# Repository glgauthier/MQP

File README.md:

# FPGA-Based Real-Time SLAM

This repository contains code and miscellaneous content for our [Major Qualifying Project](https://www.wpi.edu/academics/ece/mqp.html). 

This project created a proof of concept SLAM sensor suite capable of remotely observing and mapping areas by combining real-time stereo camera imagery with distance measurements and localization data to generate a 3D depth map and 2D floorplan of its environment. The system used a Xilinx Zynq SoC containing an embedded ARM processor and FPGA fabric, and implemented unique SLAM processing functionality using both embedded software and parallelized custom logic.

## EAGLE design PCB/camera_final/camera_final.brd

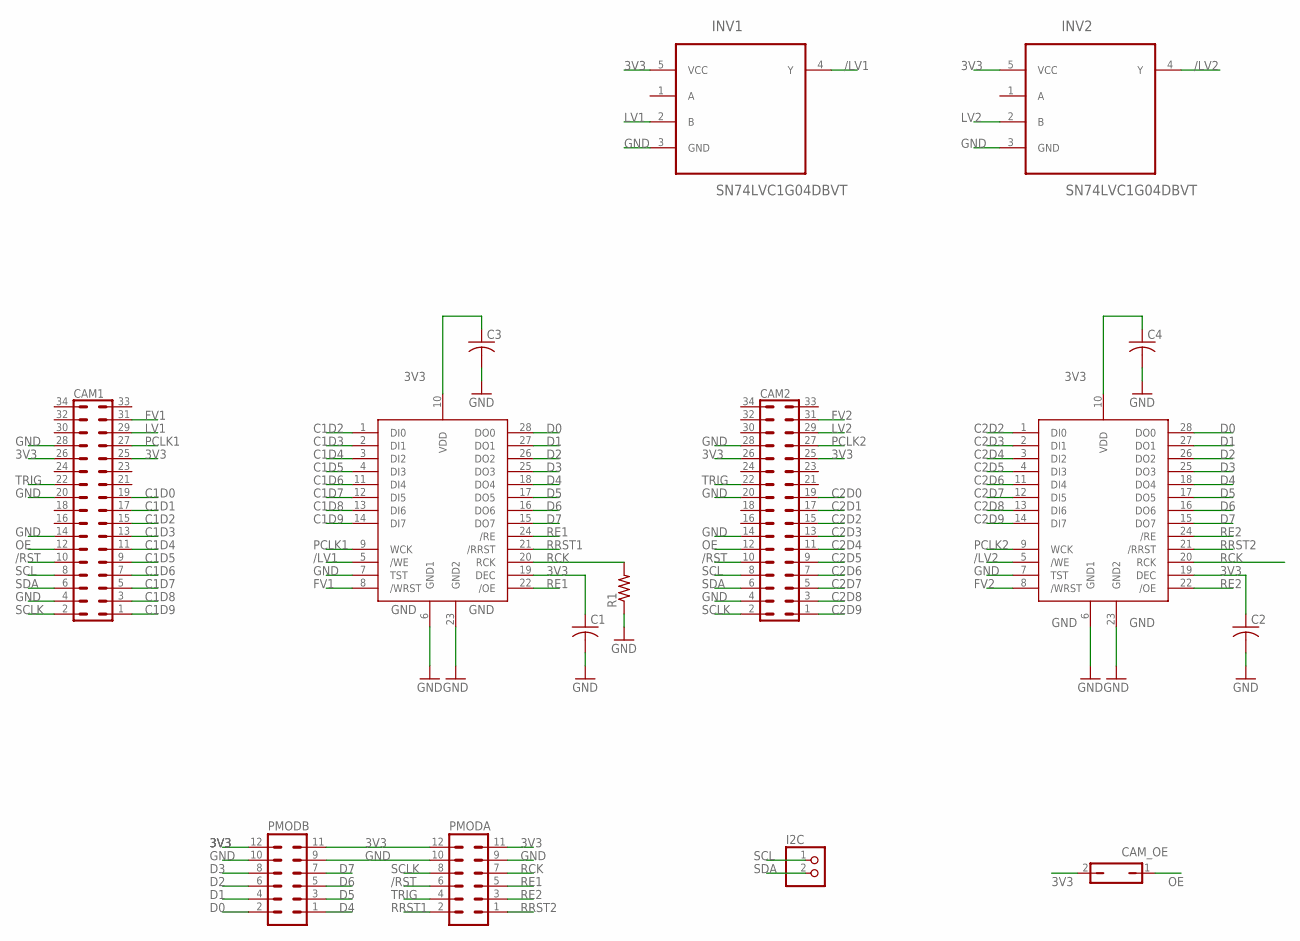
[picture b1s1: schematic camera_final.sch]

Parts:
C1, C2, C3, C4: C-USC0805K; C0805K
CAM1, CAM2: PHB_1MM27_2X17_SNT
CAM_OE: JP1Q; JP1
I2C: PINHD-1X2; 1X02
INV1, INV2: SN74LVC1G04DBVT; SOT95P280X145-5N
PMODA: MA06-2
PMODB: MA06-2
R1: R-US_R0805; R0805
U$1, U$2: AL422B; SOP28

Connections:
3V3: C1.1, C2.1, C3.1, C4.1, CAM1.25, CAM1.26, CAM2.25, CAM2.26, CAM_OE.2, INV1.5 (VCC), INV2.5 (VCC), PMODA.11, PMODA.12, PMODB.11, PMODB.12, U$1.10 (VDD), U$1.19 (DEC), U$2.10 (VDD), U$2.19 (DEC)
/LV1: INV1.4 (Y), U$2.5 (/WE)
/LV2: INV2.4 (Y), U$1.5 (/WE)
/RST: CAM1.10, CAM2.10, PMODA.6
C1D0: CAM1.19
C1D1: CAM1.17
C1D2: CAM1.15, U$2.1 (DI0)
C1D3: CAM1.13, U$2.2 (DI1)
C1D4: CAM1.11, U$2.3 (DI2)
C1D5: CAM1.9, U$2.4 (DI3)
C1D6: CAM1.7, U$2.11 (DI4)
C1D7: CAM1.5, U$2.12 (DI5)
C1D8: CAM1.3, U$2.13 (DI6)
C1D9: CAM1.1, U$2.14 (DI7)
C2D0: CAM2.19
C2D1: CAM2.17
C2D2: CAM2.15, U$1.1 (DI0)
C2D3: CAM2.13, U$1.2 (DI1)
C2D4: CAM2.11, U$1.3 (DI2)
C2D5: CAM2.9, U$1.4 (DI3)
C2D6: CAM2.7, U$1.11 (DI4)
C2D7: CAM2.5, U$1.12 (DI5)
C2D8: CAM2.3, U$1.13 (DI6)
C2D9: CAM2.1, U$1.14 (DI7)
D0: PMODB.2, U$1.28 (DO0), U$2.28 (DO0)
D1: PMODB.4, U$1.27 (DO1), U$2.27 (DO1)
D2: PMODB.6, U$1.26 (DO2), U$2.26 (DO2)
D3: PMODB.8, U$1.25 (DO3), U$2.25 (DO3)
D4: PMODB.1, U$1.18 (DO4), U$2.18 (DO4)
D5: PMODB.3, U$1.17 (DO5), U$2.17 (DO5)
D6: PMODB.5, U$1.16 (DO6), U$2.16 (DO6)
D7: PMODB.7, U$1.15 (DO7), U$2.15 (DO7)
FV1: CAM1.31, U$2.8 (/WRST)
FV2: CAM2.31, U$1.8 (/WRST)
GND: C1.2, C2.2, C3.2, C4.2, CAM1.4, CAM1.14, CAM1.20, CAM1.28, CAM2.4, CAM2.14, CAM2.20, CAM2.28, INV1.3 (GND), INV2.3 (GND), PMODA.9, PMODA.10, PMODB.9, PMODB.10, R1.1, U$1.6 (GND1), U$1.7 (TST), U$1.23 (GND2), U$2.6 (GND1), U$2.7 (TST), U$2.23 (GND2)
LV1: CAM1.29, INV1.2 (B)
LV2: CAM2.29, INV2.2 (B)
OE: CAM1.12, CAM2.12, CAM_OE.1
PCLK1: CAM1.27, U$2.9 (WCK)
PCLK2: CAM2.27, U$1.9 (WCK)
RCK: PMODA.7, R1.2, U$1.20 (RCK), U$2.20 (RCK)
RE1: PMODA.5, U$2.22 (/OE), U$2.24 (/RE)
RE2: PMODA.3, U$1.22 (/OE), U$1.24 (/RE)
RRST1: PMODA.2, U$2.21 (/RRST)
RRST2: PMODA.1, U$1.21 (/RRST)
SCL: CAM1.8, CAM2.8, I2C.1
SCLK: CAM1.2, CAM2.2, PMODA.8
SDA: CAM1.6, CAM2.6, I2C.2
TRIG: CAM1.22, CAM2.22, PMODA.4

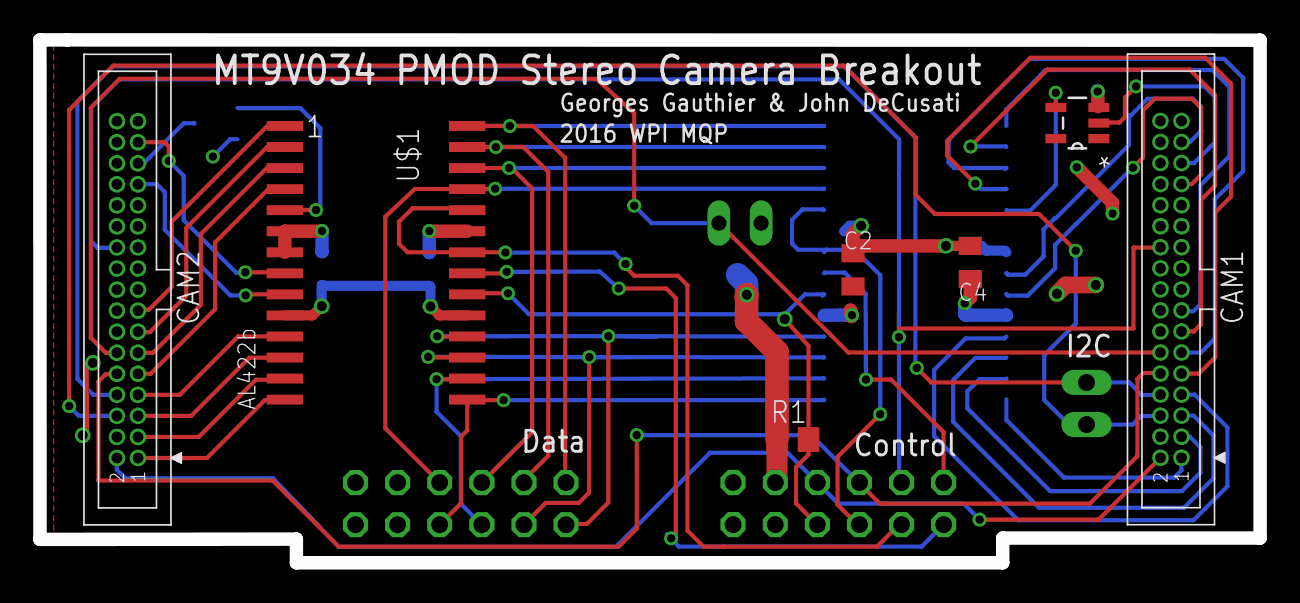
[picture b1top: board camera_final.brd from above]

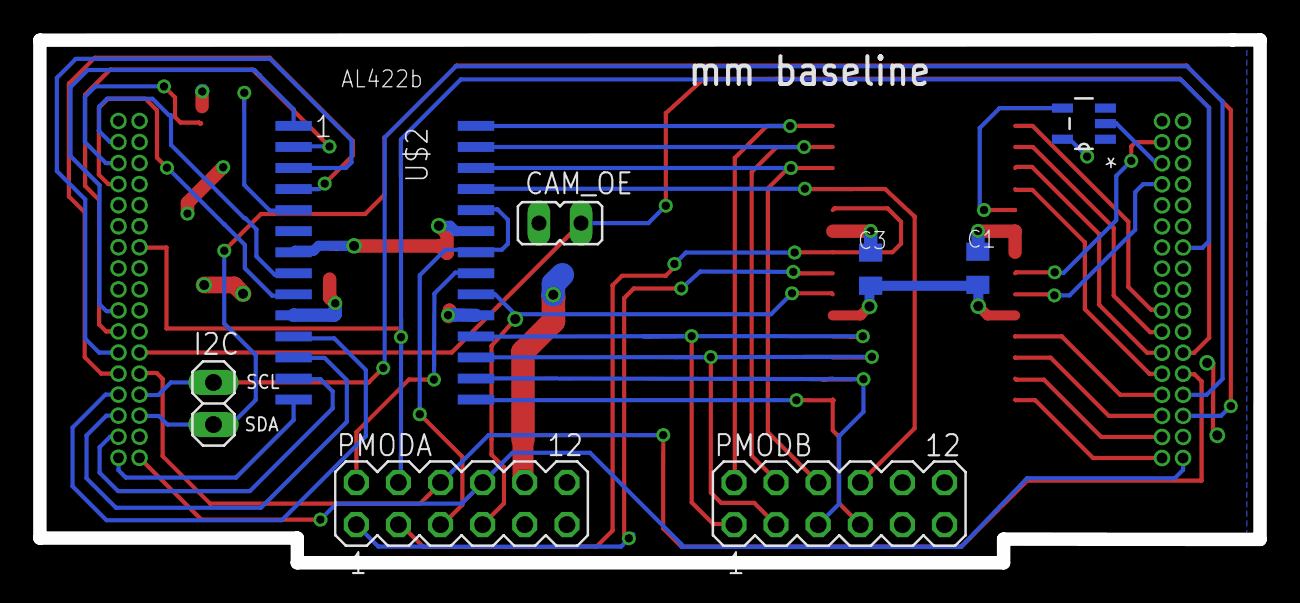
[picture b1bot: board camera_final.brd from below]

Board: 2 copper layers, 73.6 x 31.5 mm, 15 parts (8 on the bottom side), 45 nets.

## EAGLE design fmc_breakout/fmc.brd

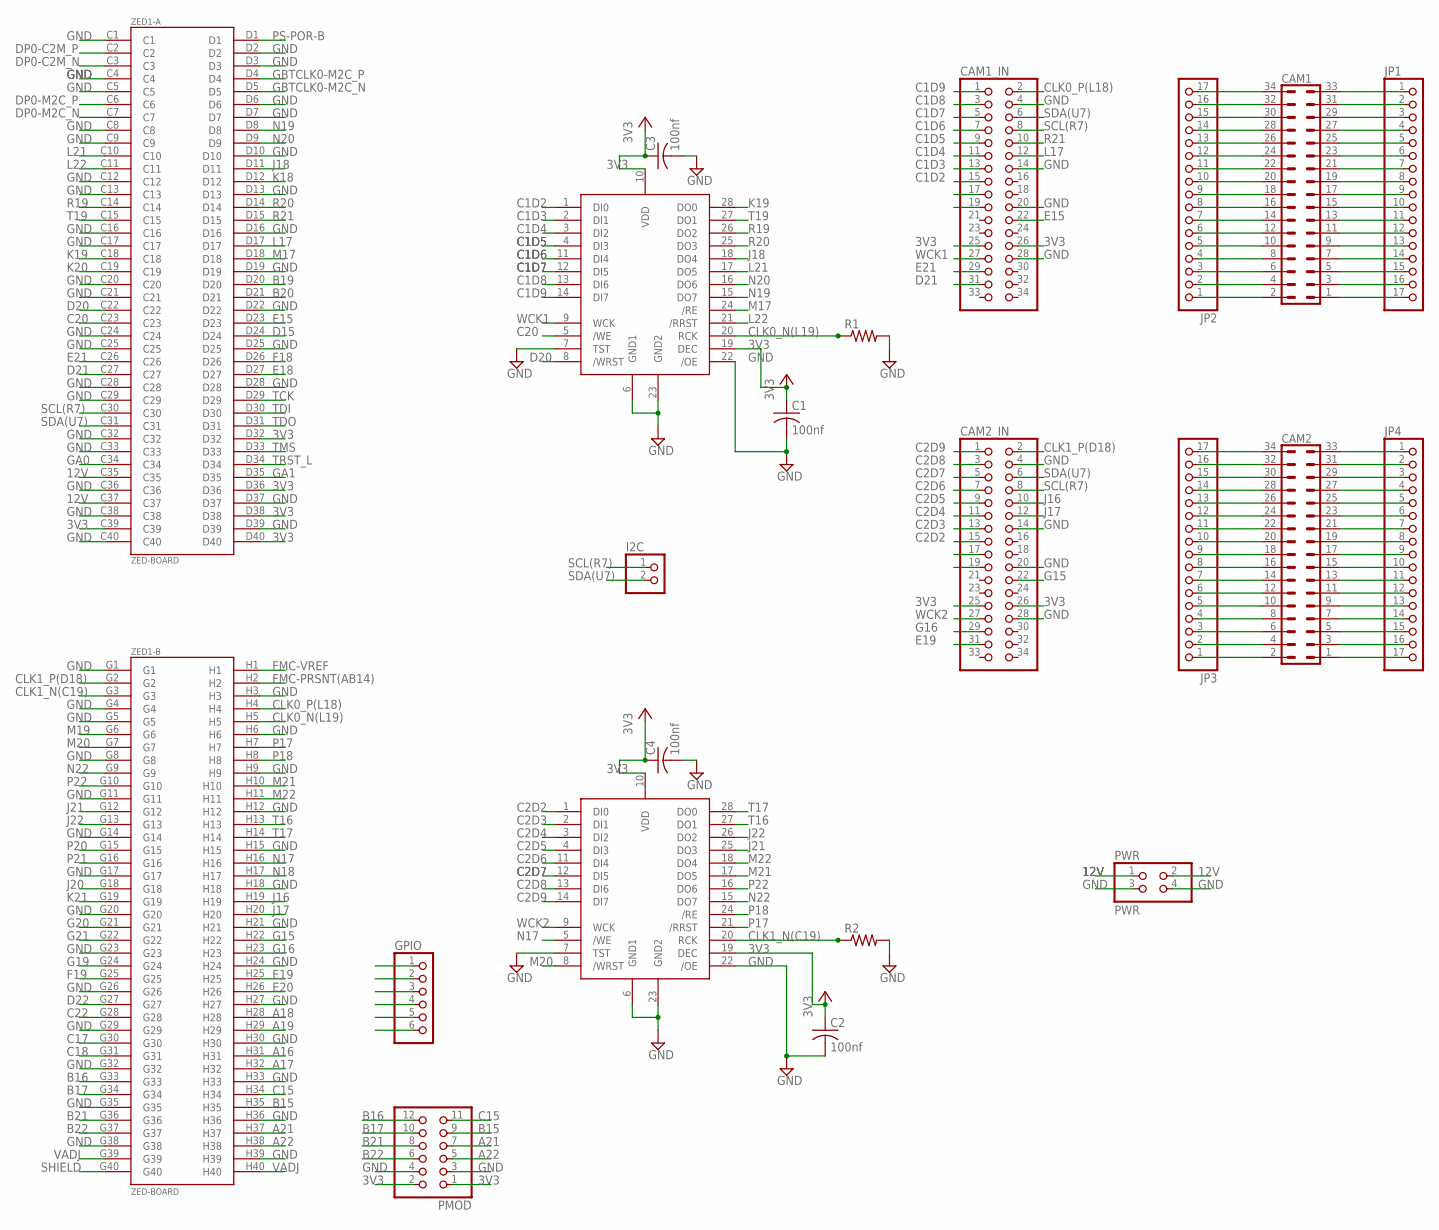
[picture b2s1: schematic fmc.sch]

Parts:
AL422B_2: CAM2_FIFO; SOP28
ALA22B_1: CAM1_FIFO; SOP28
C1, C2, C3, C4: 100nf; C025-024X044
CAM1, CAM2: PHB_1MM27_2X17_SNT
CAM1_IN, CAM2_IN: PINHD-2X17; 2X17
GPIO: PINHD-1X6; 1X06
I2C: PINHD-1X2; 1X02
JP1, JP2, JP3, JP4: PINHD-1X17; 1X17
PMOD: PINHD-2X6; 2X06
PWR: PWR; 2X02
R1, R2: R-US_M0805; M0805
ZED1: ZED-BOARD; ASP-134604-01

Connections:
3V3: AL422B_2.10 (VDD), AL422B_2.19 (DEC), ALA22B_1.10 (VDD), ALA22B_1.19 (DEC), C1.1, C2.1, C3.1, C4.1, CAM1_IN.25, CAM1_IN.26, CAM2_IN.25, CAM2_IN.26, GPIO.6, PMOD.1, PMOD.2, ZED1.C39, ZED1.D32, ZED1.D36, ZED1.D38, ZED1.D40
12V: PWR.1, PWR.2, ZED1.C35, ZED1.C37
A16: GPIO.3, ZED1.H31
A17: GPIO.4, ZED1.H32
A18: GPIO.1, ZED1.H28
A19: GPIO.2, ZED1.H29
A21: PMOD.7, ZED1.H37
A22: PMOD.5, ZED1.H38
B15: PMOD.9, ZED1.H35
B16: PMOD.12, ZED1.G33
B17: PMOD.10, ZED1.G34
B19: ZED1.D20
B20: ZED1.D21
B21: PMOD.8, ZED1.G36
B22: PMOD.6, ZED1.G37
C1D2: ALA22B_1.1 (DI0), CAM1_IN.15
C1D3: ALA22B_1.2 (DI1), CAM1_IN.13
C1D4: ALA22B_1.3 (DI2), CAM1_IN.11
C1D5: ALA22B_1.4 (DI3), CAM1_IN.9
C1D6: ALA22B_1.11 (DI4), CAM1_IN.7
C1D7: ALA22B_1.12 (DI5), CAM1_IN.5
C1D8: ALA22B_1.13 (DI6), CAM1_IN.3
C1D9: ALA22B_1.14 (DI7), CAM1_IN.1
C2D2: AL422B_2.1 (DI0), CAM2_IN.15
C2D3: AL422B_2.2 (DI1), CAM2_IN.13
C2D4: AL422B_2.3 (DI2), CAM2_IN.11
C2D5: AL422B_2.4 (DI3), CAM2_IN.9
C2D6: AL422B_2.11 (DI4), CAM2_IN.7
C2D7: AL422B_2.12 (DI5), CAM2_IN.5
C2D8: AL422B_2.13 (DI6), CAM2_IN.3
C2D9: AL422B_2.14 (DI7), CAM2_IN.1
C15: PMOD.11, ZED1.H34
C17: ZED1.G30
C18: ZED1.G31
C20: ALA22B_1.5 (/WE), ZED1.C23
C22: ZED1.G28
CLK0_N(L19): ALA22B_1.20 (RCK), R1.1, ZED1.H5
CLK0_P(L18): CAM1_IN.2, ZED1.H4
CLK1_N(C19): AL422B_2.20 (RCK), R2.1, ZED1.G3
CLK1_P(D18): CAM2_IN.2, ZED1.G2
D15: ZED1.D24
D20: ALA22B_1.8 (/WRST), ZED1.C22
D21: CAM1_IN.31, ZED1.C27
D22: ZED1.G27
DP0-C2M_N: ZED1.C3
DP0-C2M_P: ZED1.C2
DP0-M2C_N: ZED1.C7
DP0-M2C_P: ZED1.C6
E15: CAM1_IN.22, ZED1.D23
E18: ZED1.D27
E19: CAM2_IN.31, ZED1.H25
E20: ZED1.H26
E21: CAM1_IN.29, ZED1.C26
F18: ZED1.D26
F19: ZED1.G25
FMC-PRSNT(AB14): ZED1.H2
FMC-VREF: ZED1.H1
G15: CAM2_IN.22, ZED1.H22
G16: CAM2_IN.29, ZED1.H23
G19: ZED1.G24
G20: ZED1.G21
G21: ZED1.G22
GA0: ZED1.C34
GA1: ZED1.D35
GBTCLK0-M2C_N: ZED1.D5
GBTCLK0-M2C_P: ZED1.D4
GND: AL422B_2.6 (GND1), AL422B_2.7 (TST), AL422B_2.22 (/OE), AL422B_2.23 (GND2), ALA22B_1.6 (GND1), ALA22B_1.7 (TST), ALA22B_1.22 (/OE), ALA22B_1.23 (GND2), C1.2, C2.2, C3.2, C4.2, CAM1_IN.4, CAM1_IN.14, CAM1_IN.20, CAM1_IN.28, CAM2_IN.4, CAM2_IN.14, CAM2_IN.20, CAM2_IN.28, GPIO.5, PMOD.3, PMOD.4, PWR.3, PWR.4, R1.2, R2.2, ZED1.C1, ZED1.C4, ZED1.C5, ZED1.C8, ZED1.C9, ZED1.C12, ZED1.C13, ZED1.C16, ZED1.C17, ZED1.C20, ZED1.C21, ZED1.C24, ZED1.C25, ZED1.C28, ZED1.C29, ZED1.C32, ZED1.C33, ZED1.C36, ZED1.C38, ZED1.C40, ZED1.D2, ZED1.D3, ZED1.D6, ZED1.D7, ZED1.D10, ZED1.D13, ZED1.D16, ZED1.D19, ZED1.D22, ZED1.D25, ZED1.D28, ZED1.D37, ZED1.D39, ZED1.G1, ZED1.G4, ZED1.G5, ZED1.G8, ZED1.G11, ZED1.G14, ZED1.G17, ZED1.G20, ZED1.G23, ZED1.G26, ZED1.G29, ZED1.G32, ZED1.G35, ZED1.G38, ZED1.H3, ZED1.H6, ZED1.H9, ZED1.H12, ZED1.H15, ZED1.H18, ZED1.H21, ZED1.H24, ZED1.H27, ZED1.H30, ZED1.H33, ZED1.H36, ZED1.H39
J16: CAM2_IN.10, ZED1.H19
J17: CAM2_IN.12, ZED1.H20
J18: ALA22B_1.18 (DO4), ZED1.D11
J20: ZED1.G18
J21: AL422B_2.25 (DO3), ZED1.G12
J22: AL422B_2.26 (DO2), ZED1.G13
K18: ZED1.D12
K19: ALA22B_1.28 (DO0), ZED1.C18
K20: ZED1.C19
K21: ZED1.G19
L17: CAM1_IN.12, ZED1.D17
L21: ALA22B_1.17 (DO5), ZED1.C10
L22: ALA22B_1.21 (/RRST), ZED1.C11
M17: ALA22B_1.24 (/RE), ZED1.D18
M19: ZED1.G6
M20: AL422B_2.8 (/WRST), ZED1.G7
M21: AL422B_2.17 (DO5), ZED1.H10
M22: AL422B_2.18 (DO4), ZED1.H11
N17: AL422B_2.5 (/WE), ZED1.H16
N18: ZED1.H17
N19: ALA22B_1.15 (DO7), ZED1.D8
N20: ALA22B_1.16 (DO6), ZED1.D9
N22: AL422B_2.15 (DO7), ZED1.G9
unnamed: CAM1.34, JP2.17
unnamed: CAM1.32, JP2.16
unnamed: CAM1.30, JP2.15
unnamed: CAM1.28, JP2.14
unnamed: CAM1.26, JP2.13
unnamed: CAM1.24, JP2.12
unnamed: CAM1.22, JP2.11
unnamed: CAM1.20, JP2.10
unnamed: CAM1.18, JP2.9
unnamed: CAM1.16, JP2.8
unnamed: CAM1.14, JP2.7
unnamed: CAM1.12, JP2.6
unnamed: CAM1.10, JP2.5
unnamed: CAM1.8, JP2.4
unnamed: CAM1.6, JP2.3
unnamed: CAM1.4, JP2.2
unnamed: CAM1.2, JP2.1
unnamed: CAM1.33, JP1.1
unnamed: CAM1.31, JP1.2
unnamed: CAM1.29, JP1.3
unnamed: CAM1.27, JP1.4
unnamed: CAM1.25, JP1.5
unnamed: CAM1.23, JP1.6
unnamed: CAM1.21, JP1.7
unnamed: CAM1.19, JP1.8
unnamed: CAM1.17, JP1.9
unnamed: CAM1.15, JP1.10
unnamed: CAM1.13, JP1.11
unnamed: CAM1.11, JP1.12
unnamed: CAM1.9, JP1.13
unnamed: CAM1.7, JP1.14
unnamed: CAM1.5, JP1.15
unnamed: CAM1.3, JP1.16
unnamed: CAM1.1, JP1.17
unnamed: CAM2.33, JP4.1
unnamed: CAM2.31, JP4.2
unnamed: CAM2.29, JP4.3
unnamed: CAM2.27, JP4.4
unnamed: CAM2.25, JP4.5
unnamed: CAM2.23, JP4.6
unnamed: CAM2.21, JP4.7
unnamed: CAM2.19, JP4.8
unnamed: CAM2.17, JP4.9
unnamed: CAM2.15, JP4.10
unnamed: CAM2.13, JP4.11
unnamed: CAM2.11, JP4.12
unnamed: CAM2.9, JP4.13
unnamed: CAM2.7, JP4.14
unnamed: CAM2.5, JP4.15
unnamed: CAM2.3, JP4.16
unnamed: CAM2.1, JP4.17
unnamed: CAM2.34, JP3.17
unnamed: CAM2.32, JP3.16
unnamed: CAM2.30, JP3.15
unnamed: CAM2.28, JP3.14
unnamed: CAM2.26, JP3.13
unnamed: CAM2.24, JP3.12
unnamed: CAM2.22, JP3.11
unnamed: CAM2.20, JP3.10
unnamed: CAM2.18, JP3.9
unnamed: CAM2.16, JP3.8
unnamed: CAM2.14, JP3.7
unnamed: CAM2.12, JP3.6
unnamed: CAM2.10, JP3.5
unnamed: CAM2.8, JP3.4
unnamed: CAM2.6, JP3.3
unnamed: CAM2.4, JP3.2
unnamed: CAM2.2, JP3.1
P17: AL422B_2.21 (/RRST), ZED1.H7
P18: AL422B_2.24 (/RE), ZED1.H8
P20: ZED1.G15
P21: ZED1.G16
P22: AL422B_2.16 (DO6), ZED1.G10
PS-POR-B: ZED1.D1
R19: ALA22B_1.26 (DO2), ZED1.C14
R20: ALA22B_1.25 (DO3), ZED1.D14
R21: CAM1_IN.10, ZED1.D15
SCL(R7): CAM1_IN.8, CAM2_IN.8, I2C.1, ZED1.C30
SDA(U7): CAM1_IN.6, CAM2_IN.6, I2C.2, ZED1.C31
SHIELD: ZED1.G40
T16: AL422B_2.27 (DO1), ZED1.H13
T17: AL422B_2.28 (DO0), ZED1.H14
T19: ALA22B_1.27 (DO1), ZED1.C15
TCK: ZED1.D29
TDI: ZED1.D30
TDO: ZED1.D31
TMS: ZED1.D33
TRST_L: ZED1.D34
VADJ: ZED1.G39, ZED1.H40
WCK1: ALA22B_1.9 (WCK), CAM1_IN.27
WCK2: AL422B_2.9 (WCK), CAM2_IN.27

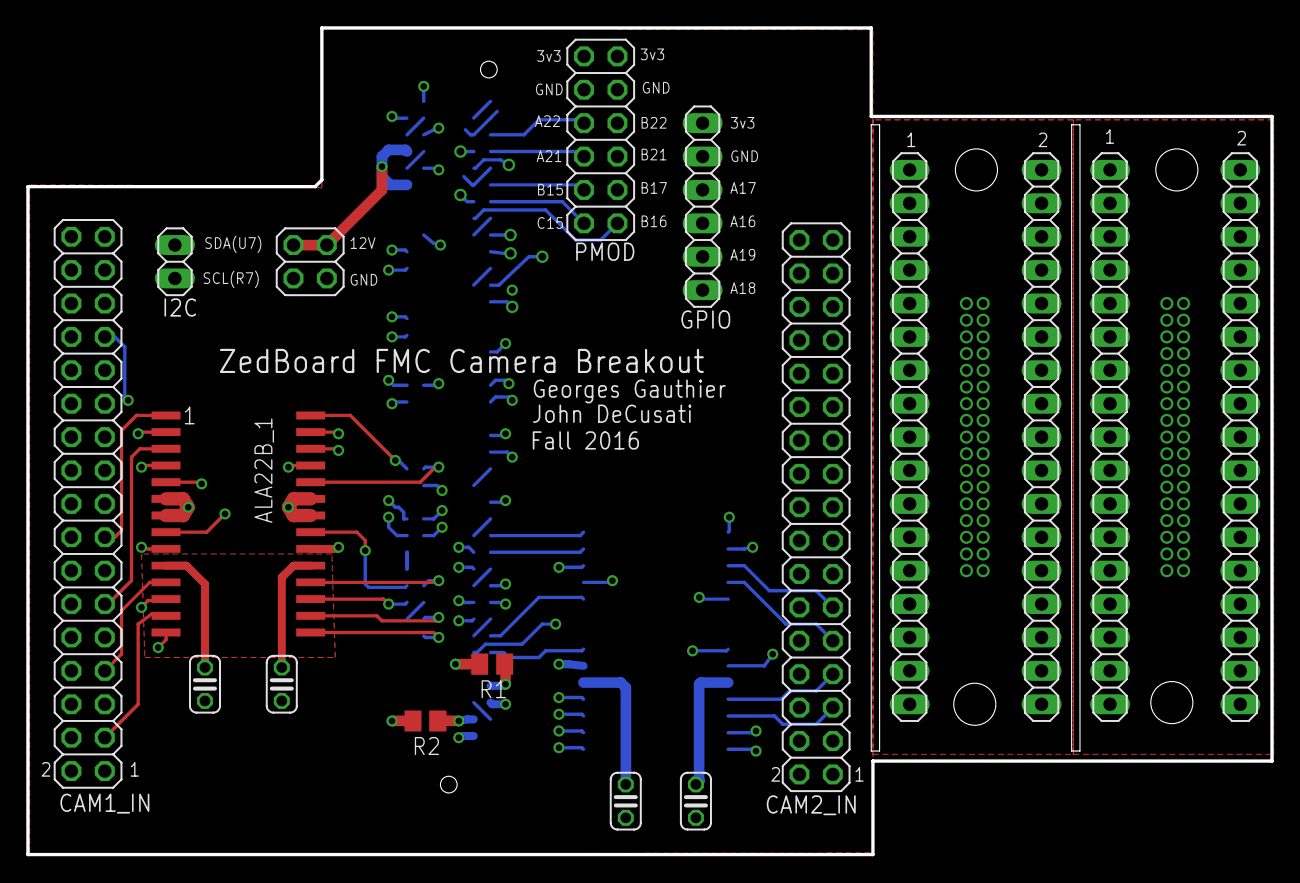
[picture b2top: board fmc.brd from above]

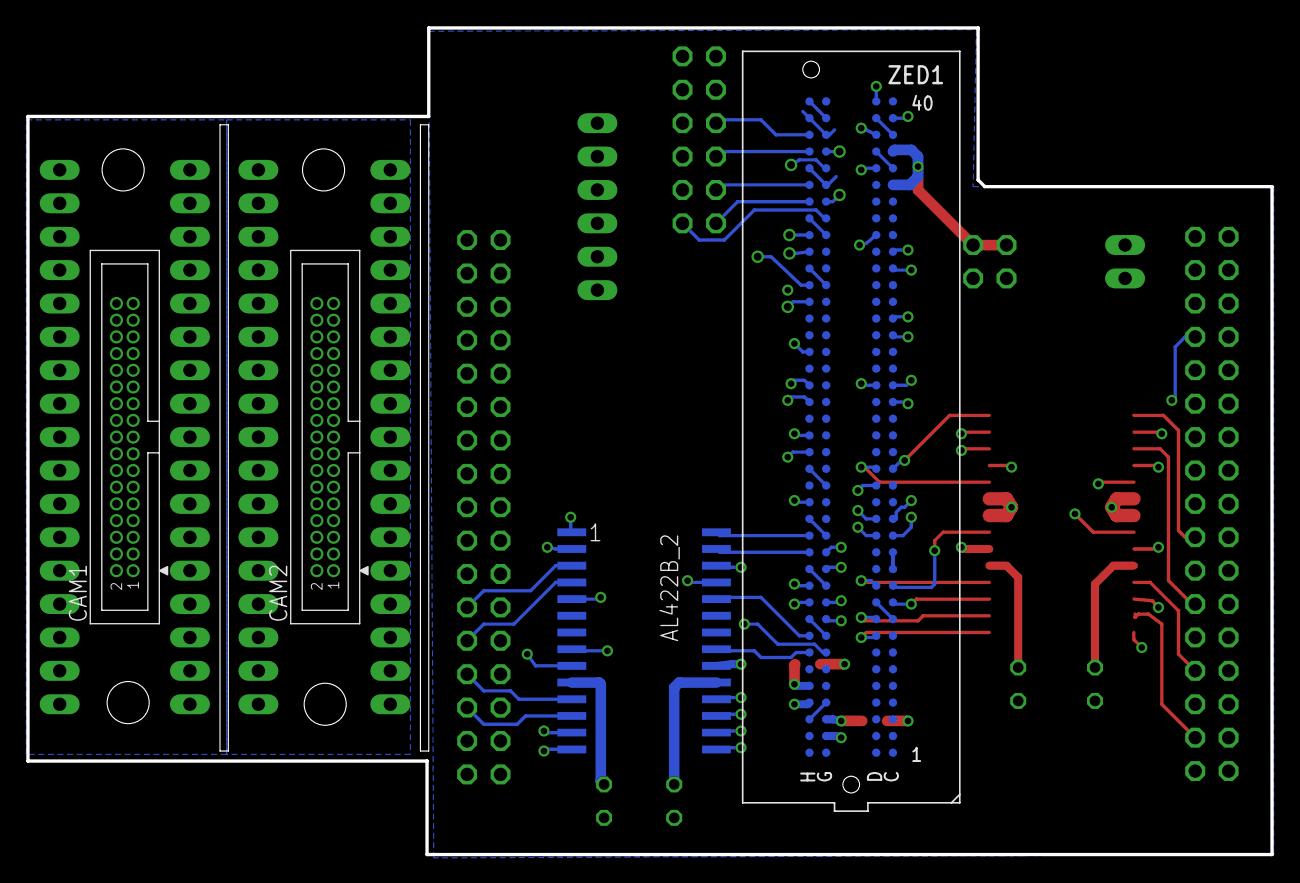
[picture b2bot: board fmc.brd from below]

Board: 4 copper layers, 94.6 x 62.9 mm, 21 parts (4 on the bottom side), 142 nets.

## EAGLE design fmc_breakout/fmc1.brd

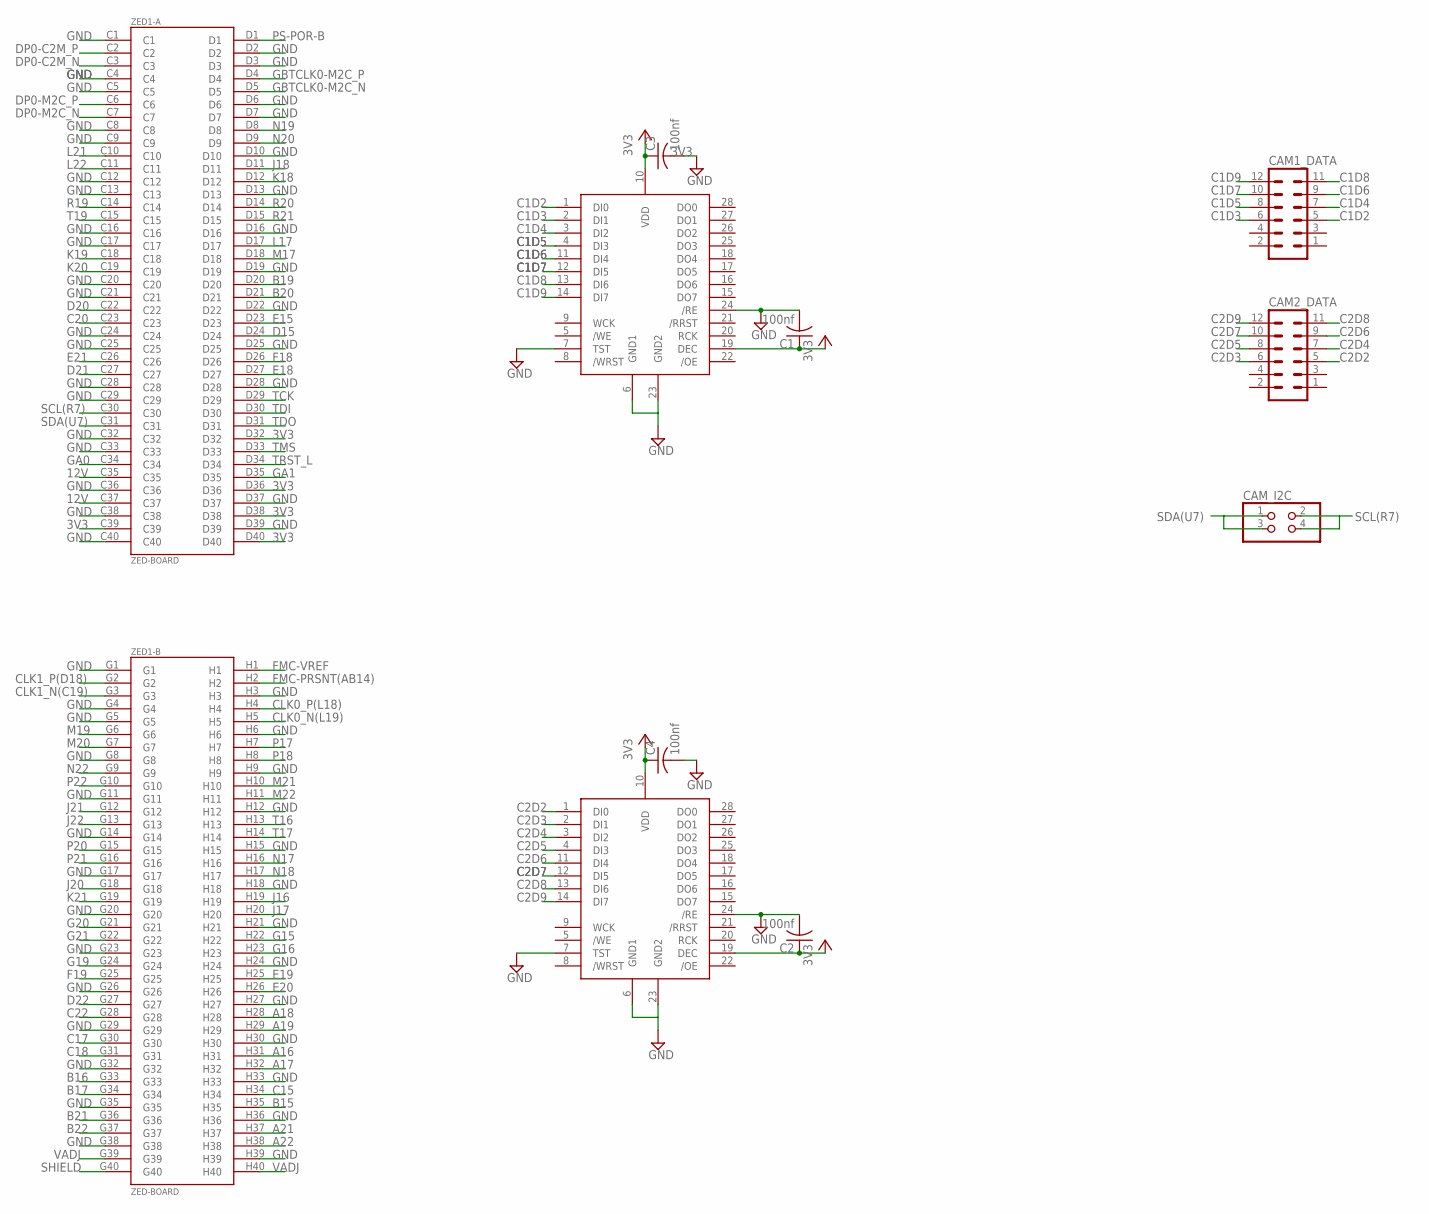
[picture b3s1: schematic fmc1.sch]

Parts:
AL422B: AL422B; SOP28
C1, C2, C3, C4: 100nf; C025-024X044
CAM1_DATA, CAM2_DATA: MA06-2
CAM_I2C: PINHD-2X2; 2X02
U$2: AL422B; SOP28
ZED1: ZED-BOARD; ASP-134604-01

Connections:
3V3: AL422B.10 (VDD), C3.1, C4.1, U$2.10 (VDD), ZED1.C39, ZED1.D32, ZED1.D36, ZED1.D38, ZED1.D40
12V: ZED1.C35, ZED1.C37
+3V3: AL422B.19 (DEC), C1.1, C2.1, U$2.19 (DEC)
A16: ZED1.H31
A17: ZED1.H32
A18: ZED1.H28
A19: ZED1.H29
A21: ZED1.H37
A22: ZED1.H38
B15: ZED1.H35
B16: ZED1.G33
B17: ZED1.G34
B19: ZED1.D20
B20: ZED1.D21
B21: ZED1.G36
B22: ZED1.G37
C1D2: AL422B.1 (DI0), CAM1_DATA.5
C1D3: AL422B.2 (DI1), CAM1_DATA.6
C1D4: AL422B.3 (DI2), CAM1_DATA.7
C1D5: AL422B.4 (DI3), CAM1_DATA.8
C1D6: AL422B.11 (DI4), CAM1_DATA.9
C1D7: AL422B.12 (DI5), CAM1_DATA.10
C1D8: AL422B.13 (DI6), CAM1_DATA.11
C1D9: AL422B.14 (DI7), CAM1_DATA.12
C2D2: CAM2_DATA.5, U$2.1 (DI0)
C2D3: CAM2_DATA.6, U$2.2 (DI1)
C2D4: CAM2_DATA.7, U$2.3 (DI2)
C2D5: CAM2_DATA.8, U$2.4 (DI3)
C2D6: CAM2_DATA.9, U$2.11 (DI4)
C2D7: CAM2_DATA.10, U$2.12 (DI5)
C2D8: CAM2_DATA.11, U$2.13 (DI6)
C2D9: CAM2_DATA.12, U$2.14 (DI7)
C15: ZED1.H34
C17: ZED1.G30
C18: ZED1.G31
C20: ZED1.C23
C22: ZED1.G28
CLK0_N(L19): ZED1.H5
CLK0_P(L18): ZED1.H4
CLK1_N(C19): ZED1.G3
CLK1_P(D18): ZED1.G2
D15: ZED1.D24
D20: ZED1.C22
D21: ZED1.C27
D22: ZED1.G27
DP0-C2M_N: ZED1.C3
DP0-C2M_P: ZED1.C2
DP0-M2C_N: ZED1.C7
DP0-M2C_P: ZED1.C6
E15: ZED1.D23
E18: ZED1.D27
E19: ZED1.H25
E20: ZED1.H26
E21: ZED1.C26
F18: ZED1.D26
F19: ZED1.G25
FMC-PRSNT(AB14): ZED1.H2
FMC-VREF: ZED1.H1
G15: ZED1.H22
G16: ZED1.H23
G19: ZED1.G24
G20: ZED1.G21
G21: ZED1.G22
GA0: ZED1.C34
GA1: ZED1.D35
GBTCLK0-M2C_N: ZED1.D5
GBTCLK0-M2C_P: ZED1.D4
GND: AL422B.6 (GND1), AL422B.7 (TST), AL422B.23 (GND2), AL422B.24 (/RE), C1.2, C2.2, C3.2, C4.2, U$2.6 (GND1), U$2.7 (TST), U$2.23 (GND2), U$2.24 (/RE), ZED1.C1, ZED1.C4, ZED1.C5, ZED1.C8, ZED1.C9, ZED1.C12, ZED1.C13, ZED1.C16, ZED1.C17, ZED1.C20, ZED1.C21, ZED1.C24, ZED1.C25, ZED1.C28, ZED1.C29, ZED1.C32, ZED1.C33, ZED1.C36, ZED1.C38, ZED1.C40, ZED1.D2, ZED1.D3, ZED1.D6, ZED1.D7, ZED1.D10, ZED1.D13, ZED1.D16, ZED1.D19, ZED1.D22, ZED1.D25, ZED1.D28, ZED1.D37, ZED1.D39, ZED1.G1, ZED1.G4, ZED1.G5, ZED1.G8, ZED1.G11, ZED1.G14, ZED1.G17, ZED1.G20, ZED1.G23, ZED1.G26, ZED1.G29, ZED1.G32, ZED1.G35, ZED1.G38, ZED1.H3, ZED1.H6, ZED1.H9, ZED1.H12, ZED1.H15, ZED1.H18, ZED1.H21, ZED1.H24, ZED1.H27, ZED1.H30, ZED1.H33, ZED1.H36, ZED1.H39
J16: ZED1.H19
J17: ZED1.H20
J18: ZED1.D11
J20: ZED1.G18
J21: ZED1.G12
J22: ZED1.G13
K18: ZED1.D12
K19: ZED1.C18
K20: ZED1.C19
K21: ZED1.G19
L17: ZED1.D17
L21: ZED1.C10
L22: ZED1.C11
M17: ZED1.D18
M19: ZED1.G6
M20: ZED1.G7
M21: ZED1.H10
M22: ZED1.H11
N17: ZED1.H16
N18: ZED1.H17
N19: ZED1.D8
N20: ZED1.D9
N22: ZED1.G9
P17: ZED1.H7
P18: ZED1.H8
P20: ZED1.G15
P21: ZED1.G16
P22: ZED1.G10
PS-POR-B: ZED1.D1
R19: ZED1.C14
R20: ZED1.D14
R21: ZED1.D15
SCL(R7): CAM_I2C.2, CAM_I2C.4, ZED1.C30
SDA(U7): CAM_I2C.1, CAM_I2C.3, ZED1.C31
SHIELD: ZED1.G40
T16: ZED1.H13
T17: ZED1.H14
T19: ZED1.C15
TCK: ZED1.D29
TDI: ZED1.D30
TDO: ZED1.D31
TMS: ZED1.D33
TRST_L: ZED1.D34
VADJ: ZED1.G39, ZED1.H40

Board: 2 copper layers, 10 parts (0 on the bottom side), 23 nets, no tracks yet.

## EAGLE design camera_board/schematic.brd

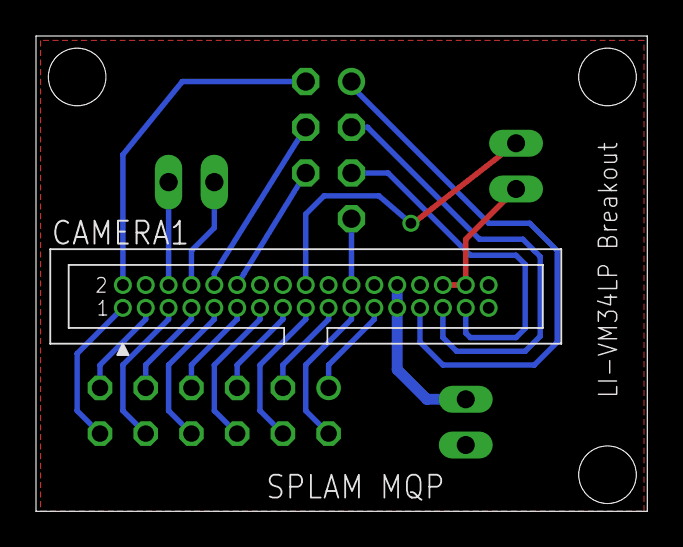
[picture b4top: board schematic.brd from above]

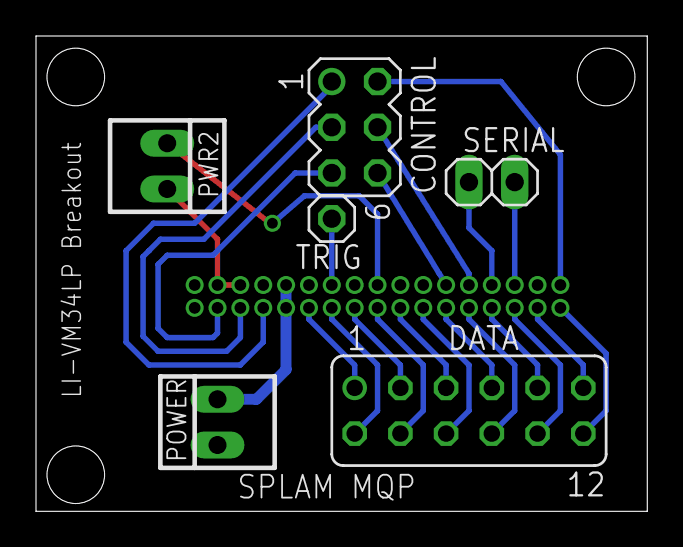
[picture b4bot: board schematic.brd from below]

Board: 2 copper layers, 34.0 x 26.4 mm, 7 parts (6 on the bottom side), 25 nets.

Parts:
CAMERA1: MT9V034; PHB_1MM27_2X17_SNT
CONTROL: MA03-2
DATA: FE06-2
POWER: MAIN; 22-23-2021
PWR2: NC; 22-23-2021
SERIAL: 1X02
TRIG: 1X01

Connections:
1.8V: CAMERA1.30, CAMERA1.32, PWR2.2
2.8V: CAMERA1.18, PWR2.1
GND: CAMERA1.4, CAMERA1.14, CAMERA1.20, CAMERA1.28, POWER.1
unnamed: CAMERA1.23, DATA.1
unnamed: CAMERA1.21, DATA.2
unnamed: CAMERA1.19, DATA.3
unnamed: CAMERA1.17, DATA.4
unnamed: CAMERA1.15, DATA.5
unnamed: CAMERA1.13, DATA.6
unnamed: CAMERA1.11, DATA.7
unnamed: CAMERA1.9, DATA.8
unnamed: CAMERA1.7, DATA.9
unnamed: CAMERA1.5, DATA.10
unnamed: CAMERA1.3, DATA.11
unnamed: CAMERA1.1, DATA.12
unnamed: CAMERA1.12, CONTROL.6
unnamed: CAMERA1.10, CONTROL.4
unnamed: CAMERA1.2, CONTROL.2
unnamed: CAMERA1.31, CONTROL.5
unnamed: CAMERA1.29, CONTROL.3
unnamed: CAMERA1.27, CONTROL.1
unnamed: CAMERA1.8, SERIAL.2
unnamed: CAMERA1.6, SERIAL.1
TRIGGER: CAMERA1.22, TRIG.1
VCC: CAMERA1.25, CAMERA1.26, POWER.2

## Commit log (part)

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2016-05-05 basic web page
    added support for a landing page, about page, and timeline
2016-05-05 updated gh-pages readme.md
2016-05-05 LaTeX report
    Started working on our report in LaTeX. So far I’ve set the following
    up:
    - Formatted title page
    - Support for a Table of Contents w/ clickable links to each section
    - Acknowledgements, Abstract, and Introduction.
    Things I still need to add
2016-05-06 Background, Appendix, Minor Changes
2016-05-26 Started Camera Adapter Schematic
    - Starting with a single camera module for now, then I'll rinse and
    repeat.
    Currently done with PWR/GND and camera shutter trigger. Mapping to the
    PMOD connectors will get interesting...
2016-05-26 Completed Schematic, Started Board
2016-05-27 Updated Schematic and Board
    I'm debating on removing the ccd_data pin breakout all together - more
    to come on this
2016-05-31 removed local schematic location
2016-05-31 Deleted schematic local location
2016-05-31 Final Schematic Part II
    Need to double check and then I'll order boards
2016-05-31 FMC-LPC connector added for future breakout board project
2016-05-31 Added missing pin, finalized(?) board design
    - Missed the trigger pin, that could have been bad!
    - Double checked the layout and it looks correct
    - Passed OSHpark DRC, ERC
2016-07-10 camera reset, eagle cleanup
2016-07-10 rangefinder data
2016-07-11 UART test
    not working
2016-07-13 added BUFG for debounce CLK
    no more warnings!
2016-07-13 writing correct val; ready for tri-state & SM
2016-07-14 camera data
2016-07-15 removed "i2c" code
    not worth the time, found another route. Next up is proper power up
    sequence
2016-07-15 proper initialization sequence, scope data
    it works!
    - full i2c control from 3.3v external micro
    - able to configure control register for external trigger mode
    -> control register isn't saved between OE_N state change, so set OE_N
    high before changing camera control to trigger mode
2016-07-15 started FMC breakout
2016-07-15 FMC bus map
2016-07-15 FMC bus pins mapped to FPGA bank locations
2016-07-16 added camera data headers
2016-07-18 microblaze for camera data over UART
2016-07-19 updated fifo code, screenshots, matlab code
    - Camera -> AL422B FIFO -> Line buffer on FPGA -> Microblaze -> UART. it
    almost works!
2016-07-20 updated matlab script for showing images, cleaned up stuff
2016-07-20 added camera section to methodology
2016-07-21 100% working images
    finally!
    I was leaving FIFO_RDEN on for an extra 2 clock cycles, so my read
    pointer was 2 pixels further ahead of where it should have been for
    every read by the FPGA
2016-07-21 more bug fixes
2016-07-22 updating report
2016-07-22 camera operation
2016-07-22 listings line wrap
2016-07-25 semi-finished documentation of current progress
2016-07-25 proofreading
2016-07-27 Finished routing traces
2016-07-27 FMC board tweaks
2016-07-28 updated PCB file locations
2016-07-29 routing stereo camera board
2016-07-29 semi-finalized layout
2016-07-29 added board images
2016-08-01 stereo cam breakout in report
2016-08-01 checkout
2016-08-02 cam streaming test
2016-08-02 it works!
2016-08-02 eod 8/02
2016-08-03 minor tweaks
2016-08-05 misc
2016-08-13 working stereo camera board vga test
    gathering data from just cam1 for now. next step will be to add a switch
    for changing between the two
2016-08-14 added a pic
2016-08-14 one more photo
    for good measure
2016-08-14 updated report
2016-08-24 added my rangefinder stuff
2016-08-25 Added VR MQP to bibliography
2016-08-25 removed extra junk
2016-08-26 switched to vivado to start coding on zedboard
2016-08-28 ise design suite -> vivado
    created vivado ip cores, copy/pasted files from ISE design suite to
    vivado
2016-08-29 Put new picture in report
2016-08-31 Added better camera picture, fixed ref
2016-09-04 added stereo support to UART camera interface
2016-09-06 Added some matlab stuff
2016-09-06 created a uartlite ip module
2016-09-07 re-added project_2
    This is the zedboard uart module that was temporarily moved when I broke
    GitHub
2016-09-13 added i2c functionality to the uart module in sdk
2016-09-26 changed uart1 to uart0, created a new bsp to reflect uart0
2016-10-05 updating UART module, started disparity implementation
2016-10-09 Working on disparity implementation
2016-10-09 Added MATLAB disparity code
2016-10-09 put disparity code in appendix
2016-10-18 added rangefinder data processing
    ps-pl communication and data processing
2016-10-19 Disparity updates
    - Finished state for reading in image data from FIFOs
    - Dynamic search bounds for current block and disparity range
2016-10-19 Read template block data in SEPARATE state
2016-10-29 Added changes from last week
2016-10-29 Added disparity overview to report
    Still need to finish image rectification portion, waiting to get better
    calibration example images first
2016-10-30 ZedBoard VGA Camera Module
    it works!
2016-10-30 Added picture of zedboard camers test to report
2016-11-02 Pre block design
2016-11-03 Added Camera-AXI IP to block design, generated bitstream
2016-11-08 custom ip
2016-11-08 launched sdk for custom ip
2016-11-08 more tests
2016-11-09 please god let this work
2016-11-10 Disparity test bench
2016-11-17 working separation and SAD
2016-11-17 Working SAD vector search
    FINALIZE state is complete with the exception of checking output image
    data
2016-11-17 Working disparity
    Changed resultant vector data placement, now it works!
2016-11-18 output register down to 8 bits
    whoops
2016-11-22 Updating camera code
2016-11-22 Added bram, clkgen to disparity test imp
2016-11-27 Semi-working disparity
    I need to calibrate my cams
2016-11-28 Bitstream for height-corrected version
2016-12-01 Misc changes
2016-12-01 updated with newest changes
2016-12-02 Started final implementation, working disparity!
2016-12-05 one line output for correlation with rangefinder
2016-12-06 Fixed issue with output images wrapping to the left
2016-12-06 more fixes
2016-12-07 Finalized top level I/O in final imp
2016-12-07 Close of business; we'll be back tomorrow
2016-12-07 bug testing
2016-12-08 IT WORKS
2016-12-09 added PS
2016-12-09 Combined rangefinder/disparity mode
2016-12-12 scaled and averaged single-line out
2016-12-12 Finished I2C!
2016-12-12 Better smoothing algorithm
2016-12-13 clearing rangefinder data; rangefinder FSM
2016-12-13 continuous rangefinder output
2016-12-14 updated smoothing
2016-12-14 merged cam changes into final imp
2016-12-14 updated title
2016-12-14 comments
2016-12-14 IMU, Rangefinder Updates
2016-12-14 IMU updates
2016-12-14 cleaned up rangefinder code
2016-12-14 updated IMU code
2016-12-16 attempting EMIO to IMU
2016-12-17 deleted old files
2016-12-18 In the SDK - added a read command from the x and y offset registers, and calculated the compass heading and rangefinder step offset
2016-12-18 changed atan to atan2 and other minor changes
2016-12-21 IMU-rangefinder working
2016-12-21 Updated report structure
2016-12-26 began working on rangefinder part of the paper, broke the main paper tex file
2016-12-27 disparity test bench figures
2016-12-27 added IMU oscillogram
2016-12-27 continued working on the rangefinder section of the paper, didn't break the paper this time
2016-12-28 Updated Camera Stuff
2016-12-28 Broke out disparity by section
2016-12-29 more paper updates, rangefinder implementation and data processing sections
2016-12-31 more rangefinder paper updates
2017-01-02 report - minor rangefinder updates, set IMU section layout, added .coe files to appendix
2017-01-02 finalized disparity implementation section
2017-01-02 updated camera operation
2017-01-02 (hopefully) finished camera ops section
2017-01-02 wrote some of the IMU sections
2017-01-03 continued working on imu sections
2017-01-03 finalized camera hw section
2017-01-03 more paper updates
2017-01-03 more disparity
2017-01-04 idk man, words
2017-01-04 added Appendix sections and PS-PL Communication section
2017-01-04 appendix changes and ps-pl communication changes
2017-01-04 minor rangefinder edits
2017-01-04 updated gitignore for autogenerated files
2017-01-04 final del dia dos
2017-01-04 reorganized appendix
2017-01-04 structural changes
2017-01-04 don't worry about it
2017-01-04 rs232 to ttl pix
2017-01-04 system design section
2017-01-04 lol @ USB-OTG
2017-01-04 appendix numbering update
2017-01-04 combined imp. figures
2017-01-05 edited rangefinder testing
2017-01-05 finished first draft of rangefinder testing
2017-01-06 updated block diagram for background section
2017-01-06 appendix label
2017-01-06 fixed undefinded character that appeared as a ?
2017-01-06 executive summary
2017-01-06 rough draft report
2017-01-06 testing integrity
2017-01-07 emio edit fig
2017-01-07 better figure
2017-01-07 updated component selection and imu testing
2017-01-08 added conclusion
2017-01-08 combined imp in testing section
2017-01-08 minor edits to rangefinder testing
2017-01-08 minor edits to abstract and exec summary
2017-01-08 minor intro changes
2017-01-08 minor edits to system design
2017-01-08 final code changes
2017-01-08 minor rangefinder operation edits
2017-01-08 some edits to rangefinder implementation
2017-01-09 edits to rangefinder data processing, added rangefinder code to appendix
2017-01-09 edited imu operation, re-changed all PMOD to Pmod
2017-01-09 made changes to the Appendix layout
2017-01-09 edits to imu implementation
2017-01-09 minor edits to camera operation
2017-01-09 changed literally one letter in disparity implementation
2017-01-09 removed one comma from combined imp
2017-01-09 edits to imu testing
2017-01-09 edits to camera implementation
2017-01-09 edits to disparity implementation and testing
2017-01-09 camera testing picture, misc changes
2017-01-10 added labels to some scope photos
2017-01-10 past tense through intro
2017-01-10 added labels to scope photos
2017-01-11 fixed headings
2017-01-11 updated figures
2017-01-11 updated intros
2017-01-11 changed abstract to under 80 words
2017-01-11 added summary to one of the ends of the chapters
2017-01-11 changed combined imp to past tense
2017-01-11 changed intro for combined imp
2017-01-11 added intros/conclusions for each chapter
2017-01-11 more tense changes
2017-01-11 edited conclusion
2017-01-11 changed tense of imu testing
2017-01-11 minor edits to conclusion
2017-01-11 caption edit in rangefinder testing
2017-01-11 reverted hardware setup figure
2017-01-11 made labels bigger on figure 70
2017-01-11 updated some figures
2017-01-11 updated figs again
2017-01-11 edited final results
2017-01-11 revised final results
2017-01-12 changes to abstract
2017-01-12 updated abstract
2017-01-12 minor ecec summary changes
2017-01-14 minor change to exec summary
2017-01-14 updated references for revised intro
2017-01-14 minor exec summary changes
2017-01-14 intro changes
2017-01-14 more intro changes
2017-01-14 edits navigational data subsection
2017-01-14 minor edits
2017-01-15 added pictures and reference to bib
2017-01-15 cleaned final code
2017-01-15 minor updates
2017-01-15 updated photos
2017-01-15 added new photos to report
2017-01-15 added placeholders
2017-01-15 minor intro change
2017-01-16 updated background and introduction
2017-01-16 updated transitions
2017-01-16 changed could
2017-01-16 updated combined imp
2017-01-16 fixed figure
2017-01-16 edits to full system operation
2017-01-16 minor edits to exec summary
2017-01-16 updated executive summary
2017-01-16 edits to background
2017-01-16 background changes
2017-01-16 edits to system design
2017-01-16 added full revision
2017-01-18 edits to rangefinder implementation sections
2017-01-18 revised camera operation
2017-01-18 more disparity imp tweaks
2017-01-18 proofread camera implementation
2017-01-18 proofread disparity implementation
2017-01-18 updated rangefinder operation section
2017-01-18 edits to ps pl
2017-01-18 finished edits to rangefidner and imu implelemtaation
2017-01-20 edited the rest of the paper including today's edits from advisor
2017-01-20 newest changes
2017-01-23 updated conclusion
2017-01-23 full revision
2017-01-23 updated references
2017-01-23 changed all references to instantiated files
2017-01-23 updated appendix

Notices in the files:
parts and their libraries:
SparkFun-Aesthetics: Licensing: Creative Commons ShareAlike 4.0 International - https://creativecommons.org/licenses/by-sa/4.0
